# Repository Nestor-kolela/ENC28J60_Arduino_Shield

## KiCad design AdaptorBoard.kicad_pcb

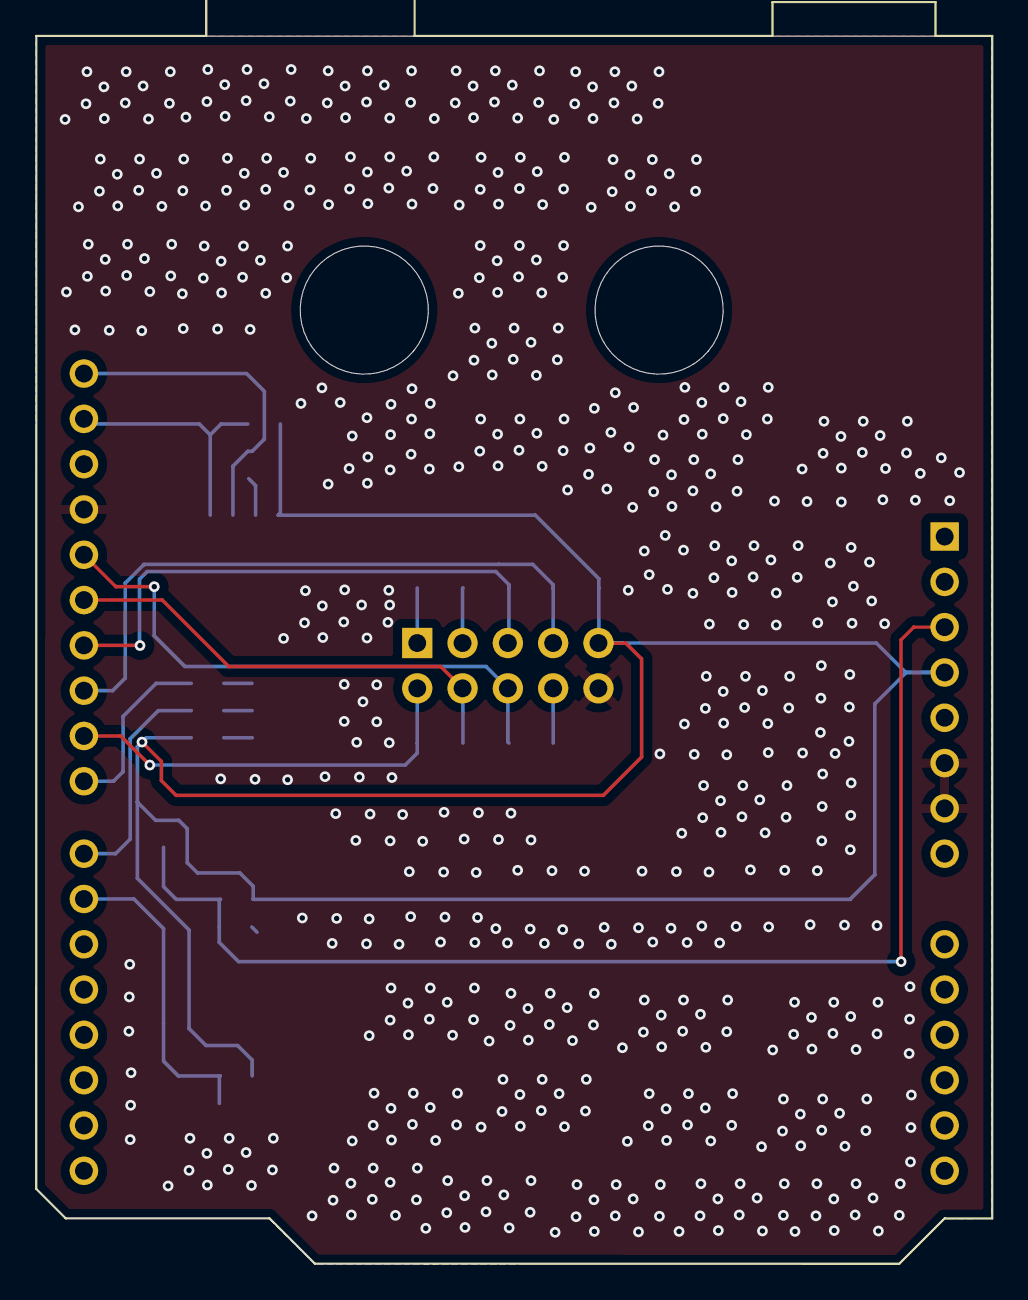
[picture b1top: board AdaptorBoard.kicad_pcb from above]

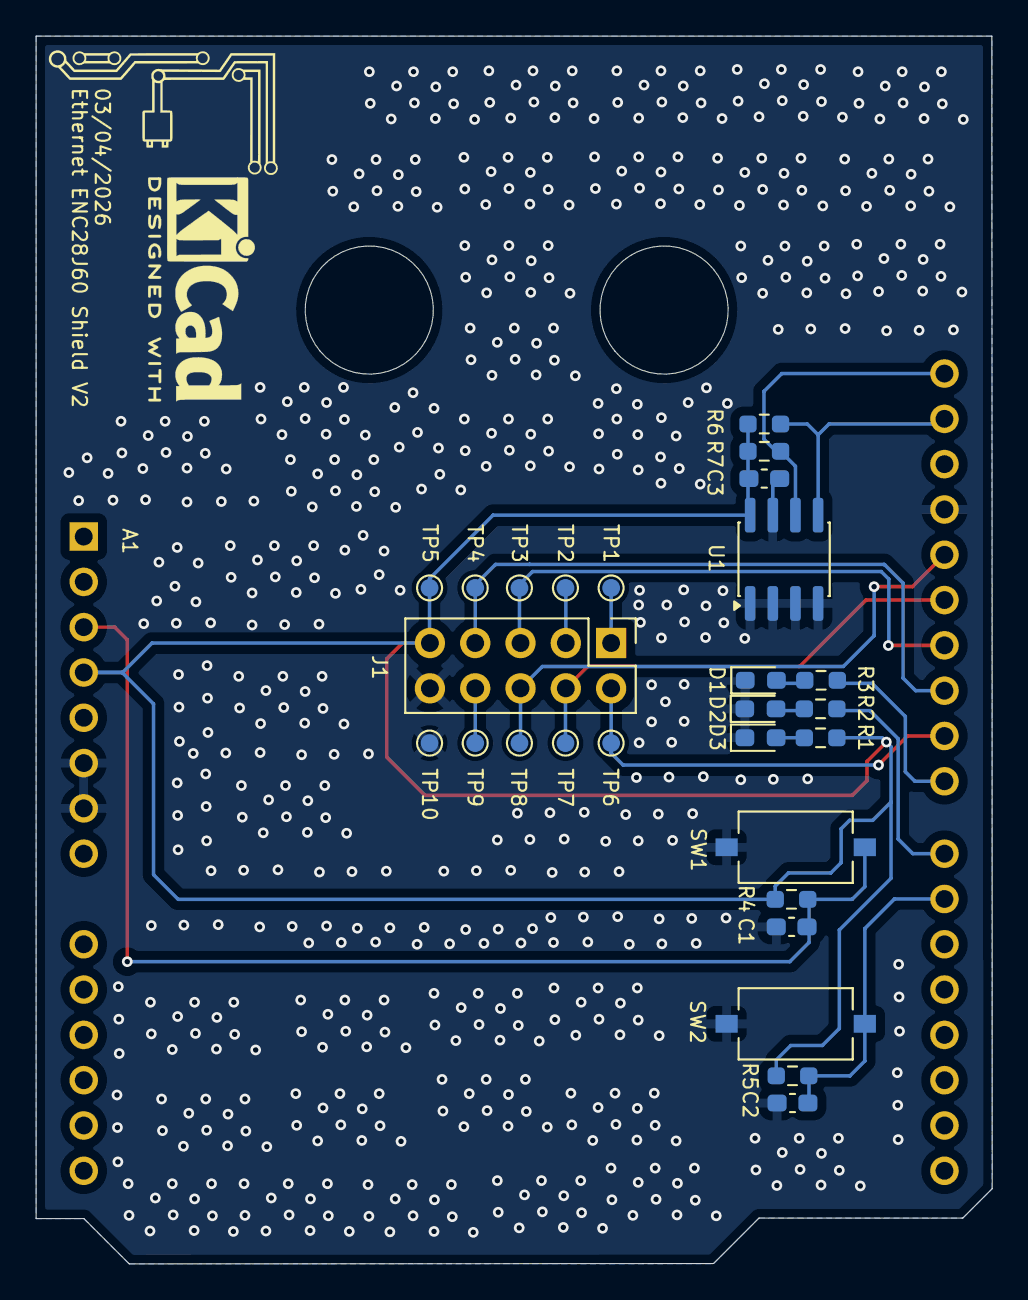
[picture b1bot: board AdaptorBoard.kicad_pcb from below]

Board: 2 copper layers, 53.6 x 68.8 mm, 28 parts (27 on the bottom side), 19 nets.

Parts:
A1: Arduino_Leonardo; Arduino_UNO_R3
C1, C2, C3: 100nF; C_0603_1608Metric_Pad1.08x0.95mm_HandSolder
D1, D2, D3: LED; LED_0603_1608Metric_Pad1.05x0.95mm_HandSolder
J1: Conn_02x05_Odd_Even; PinHeader_2x05_P2.54mm_Vertical
R1, R2, R3: 1K; R_0603_1608Metric_Pad0.98x0.95mm_HandSolder
R4, R5: 33K; R_0603_1608Metric_Pad0.98x0.95mm_HandSolder
R6, R7: 2.2K; R_0603_1608Metric_Pad0.98x0.95mm_HandSolder
SW1, SW2: SW_Push; SW_Tactile_SPST_NO_Straight_CK_PTS636Sx25SMTRLFS
TP1, TP2, TP3, TP4, TP5, TP6, TP7, TP8, TP9, TP10: TestPoint; TestPoint_Pad_D1.0mm
U1: 24LC1025; SOIC-8_3.9x4.9mm_P1.27mm

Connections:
+3.3V: A1.4 (3V3), C3.1, J1.9, R1.1, R4.1, R5.1, R6.1, R7.2, TP5.1, U1.8 (VCC)
/CLKOUT: J1.1, TP1.1
/CS: A1.25 (D10), J1.7, TP4.1
/INT: A1.24 (D9), J1.2, TP6.1
/LED_ONE: A1.22 (D7), R2.1
/LED_TWO: A1.23 (D8), R3.1
/MCU_RESET: A1.3 (~RESET), C1.1, R4.2, SW1.2
/PB_IN: A1.21 (D6), C2.1, R5.2, SW2.2
/RESET: J1.8, TP9.1
/SCK: A1.28 (D13), J1.6, TP8.1
/SI: A1.26 (D11), J1.5, TP3.1
/SO: A1.27 (D12), J1.4, TP7.1
/WOL: J1.3, TP2.1
GND: A1.6 (GND), A1.7 (GND), A1.29 (GND), C1.2, C2.2, C3.2, D1.1 (K), D2.1 (K), D3.1 (K), J1.10, SW1.1, SW2.1, TP10.1, U1.1 (A0), U1.2 (A1), U1.3 (A2), U1.4 (GND), U1.7 (WP)
unnamed: A1.32 (SCL/D3), R7.1, U1.6 (SCL)
unnamed: A1.31 (SDA/D2), R6.2, U1.5 (SDA)
unnamed: D1.2 (A), R3.2
unnamed: D2.2 (A), R2.2
unnamed: D3.2 (A), R1.2

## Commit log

2026-04-02 Add EEPROM. Change from Reset Push to input. Assign footprints and more improvements.
2026-04-03 Fix position for push buttons' holes.
2026-04-03 Finalize the PCB Design
2026-04-03 Generate gerber files.
